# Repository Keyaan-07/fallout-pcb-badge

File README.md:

# Fallout PCB Badges!!

Okay so i made the fallout badge(and everyone else who is a participant made it) andddd i added some unique that that i guess no one might have it. It is decent, it uses an stm32f030.  
So the idea i got for the LED matrix was like when i was talking to zach. He was like what are you doing unique in your PCB Badge, so i just formed the idea instantly in my mind and i stuck with it.  
Also, while writing this, i got the idea to like add an e-ink, so i am probably gonna add it later, i am really tired rn. I will be buying parts myself. yayay. The bom is js the one that the JLC fab toolkit makes sorry if it's not enough :(

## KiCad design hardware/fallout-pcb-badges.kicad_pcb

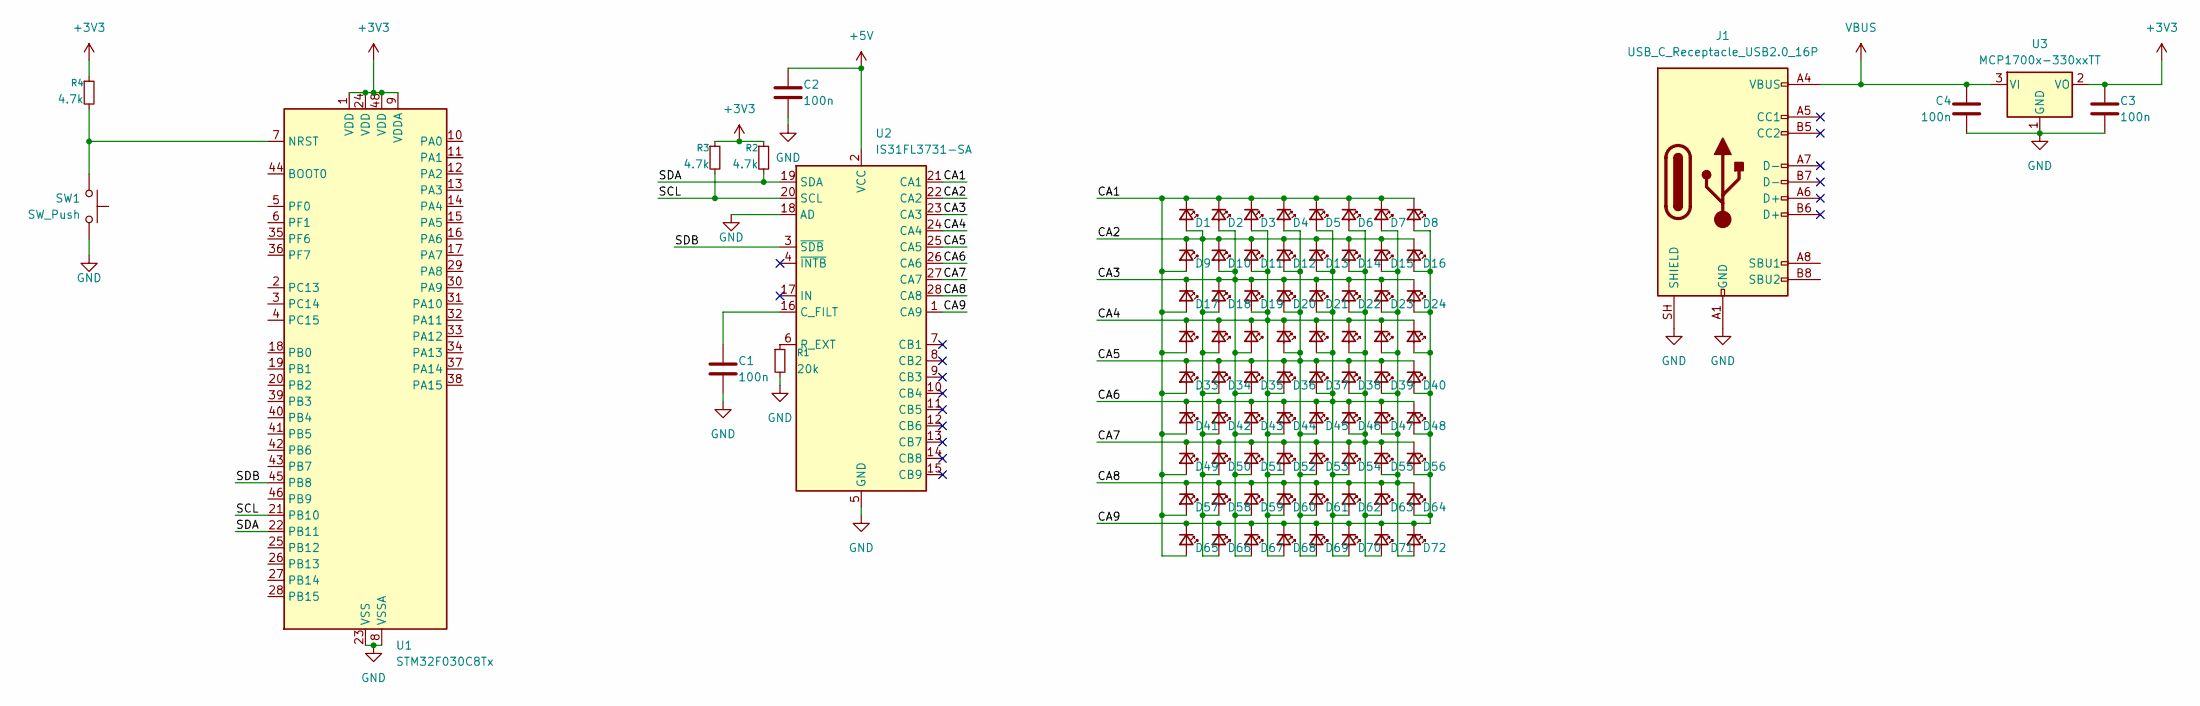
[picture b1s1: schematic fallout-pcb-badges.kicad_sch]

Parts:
C1, C2, C3, C4: 100n; C_0402_1005Metric
D1, D2, D3, D4, D5, D6, D7, D8, D9, D10, D11, D12, D13, D14, D15, D16, D17, D18, D19, D20, D21, D22, D23, D24, D25, D26, D27, D28, D29, D30, D31, D32, D33, D34, D35, D36, D37, D38, D39, D40, D41, D42, D43, D44, D45, D46, D47, D48, D49, D50, D51, D52, D53, D54, D55, D56, D57, D58, D59, D60, D61, D62, D63, D64, D65, D66, D67, D68, D69, D70, D71, D72: LED_Small; LED_0402_1005Metric
J1: USB_C_Receptacle_USB2.0_16P; USB_C_Receptacle_XKB_U262-16XN-4BVC11
R1: 20k; R_0402_1005Metric
R2, R3, R4: 4.7k; R_0402_1005Metric
SW1: SW_Push; SW_SPST_PTS810
U1: STM32F030C8Tx; LQFP-48_7x7mm_P0.5mm
U2: IS31FL3731-SA; SSOP-28_5.3x10.2mm_P0.65mm
U3: MCP1700x-330xxTT; SOT-23

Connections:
+3V3: C3.1, R2.1, R3.1, R4.1, U1.1 (VDD), U1.9 (VDDA), U1.24 (VDD), U1.48 (VDD), U3.2 (VO)
+5V: C2.1, U2.2 (VCC)
/CA1: D1.1 (K), D2.1 (K), D3.1 (K), D4.1 (K), D5.1 (K), D6.1 (K), D7.1 (K), D8.1 (K), D9.2 (A), D17.2 (A), D25.2 (A), D33.2 (A), D41.2 (A), D49.2 (A), D57.2 (A), D65.2 (A), U2.21 (CA1)
/CA2: D1.2 (A), D9.1 (K), D10.1 (K), D11.1 (K), D12.1 (K), D13.1 (K), D14.1 (K), D15.1 (K), D16.1 (K), D18.2 (A), D26.2 (A), D34.2 (A), D42.2 (A), D50.2 (A), D58.2 (A), D66.2 (A), U2.22 (CA2)
/CA3: D2.2 (A), D10.2 (A), D17.1 (K), D18.1 (K), D19.1 (K), D20.1 (K), D21.1 (K), D22.1 (K), D23.1 (K), D24.1 (K), D27.2 (A), D35.2 (A), D43.2 (A), D51.2 (A), D59.2 (A), D67.2 (A), U2.23 (CA3)
/CA4: D3.2 (A), D11.2 (A), D19.2 (A), D25.1 (K), D26.1 (K), D27.1 (K), D28.1 (K), D29.1 (K), D30.1 (K), D31.1 (K), D32.1 (K), D36.2 (A), D44.2 (A), D52.2 (A), D60.2 (A), D68.2 (A), U2.24 (CA4)
/CA5: D4.2 (A), D12.2 (A), D20.2 (A), D28.2 (A), D33.1 (K), D34.1 (K), D35.1 (K), D36.1 (K), D37.1 (K), D38.1 (K), D39.1 (K), D40.1 (K), D45.2 (A), D53.2 (A), D61.2 (A), D69.2 (A), U2.25 (CA5)
/CA6: D5.2 (A), D13.2 (A), D21.2 (A), D29.2 (A), D37.2 (A), D41.1 (K), D42.1 (K), D43.1 (K), D44.1 (K), D45.1 (K), D46.1 (K), D47.1 (K), D48.1 (K), D54.2 (A), D62.2 (A), D70.2 (A), U2.26 (CA6)
/CA7: D6.2 (A), D14.2 (A), D22.2 (A), D30.2 (A), D38.2 (A), D46.2 (A), D49.1 (K), D50.1 (K), D51.1 (K), D52.1 (K), D53.1 (K), D54.1 (K), D55.1 (K), D56.1 (K), D63.2 (A), D71.2 (A), U2.27 (CA7)
/CA8: D7.2 (A), D15.2 (A), D23.2 (A), D31.2 (A), D39.2 (A), D47.2 (A), D55.2 (A), D57.1 (K), D58.1 (K), D59.1 (K), D60.1 (K), D61.1 (K), D62.1 (K), D63.1 (K), D64.1 (K), D72.2 (A), U2.28 (CA8)
/CA9: D8.2 (A), D16.2 (A), D24.2 (A), D32.2 (A), D40.2 (A), D48.2 (A), D56.2 (A), D64.2 (A), D65.1 (K), D66.1 (K), D67.1 (K), D68.1 (K), D69.1 (K), D70.1 (K), D71.1 (K), D72.1 (K), U2.1 (CA9)
/SCL: R3.2, U1.21 (PB10), U2.20 (SCL)
/SDA: R2.2, U1.22 (PB11), U2.19 (SDA)
/SDB: U1.45 (PB8), U2.3 (~SDB)
GND: C1.2, C2.2, C3.2, C4.2, J1.A1 (GND), J1.A12 (GND), J1.B1 (GND), J1.B12 (GND), J1.SH (SHIELD), R1.2, SW1.1, U1.8 (VSSA), U1.23 (VSS), U1.47 (VSS), U2.5 (GND), U2.18 (AD), U3.1 (GND)
unnamed: R4.2, SW1.2, U1.7 (NRST)
unnamed: C1.1, U2.16 (C_FILT)
unnamed: R1.1, U2.6 (R_EXT)
VBUS: C4.1, J1.A4 (VBUS), J1.A9 (VBUS), J1.B4 (VBUS), J1.B9 (VBUS), U3.3 (VI)

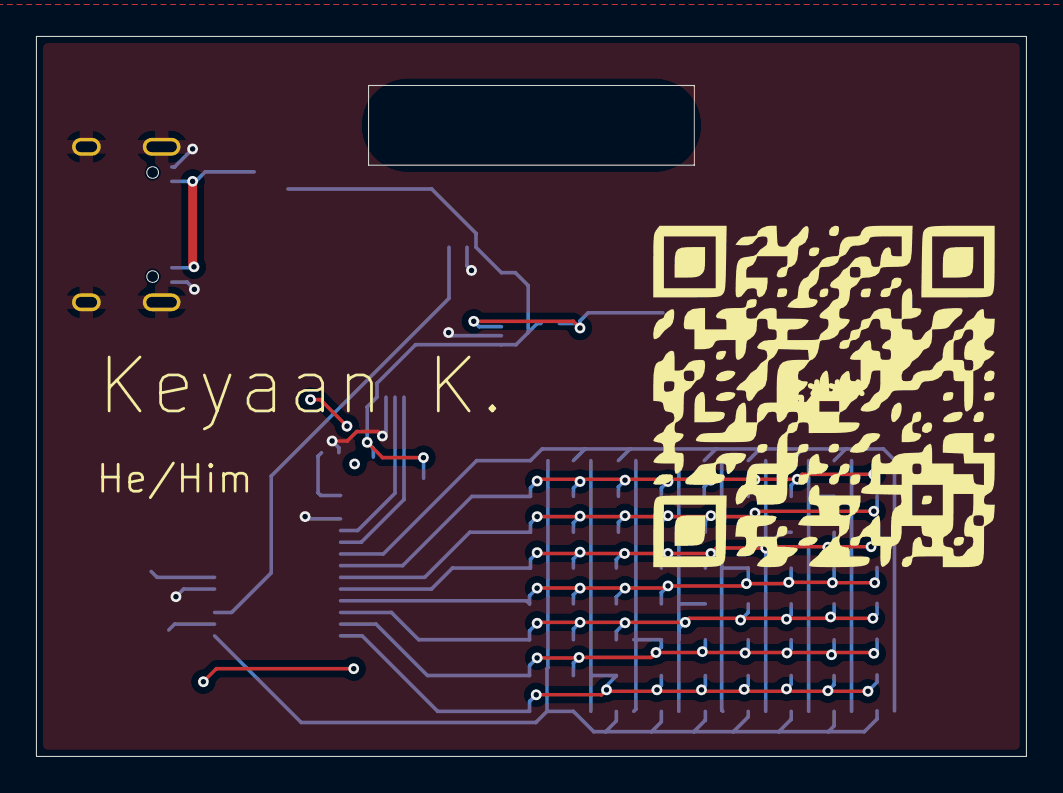
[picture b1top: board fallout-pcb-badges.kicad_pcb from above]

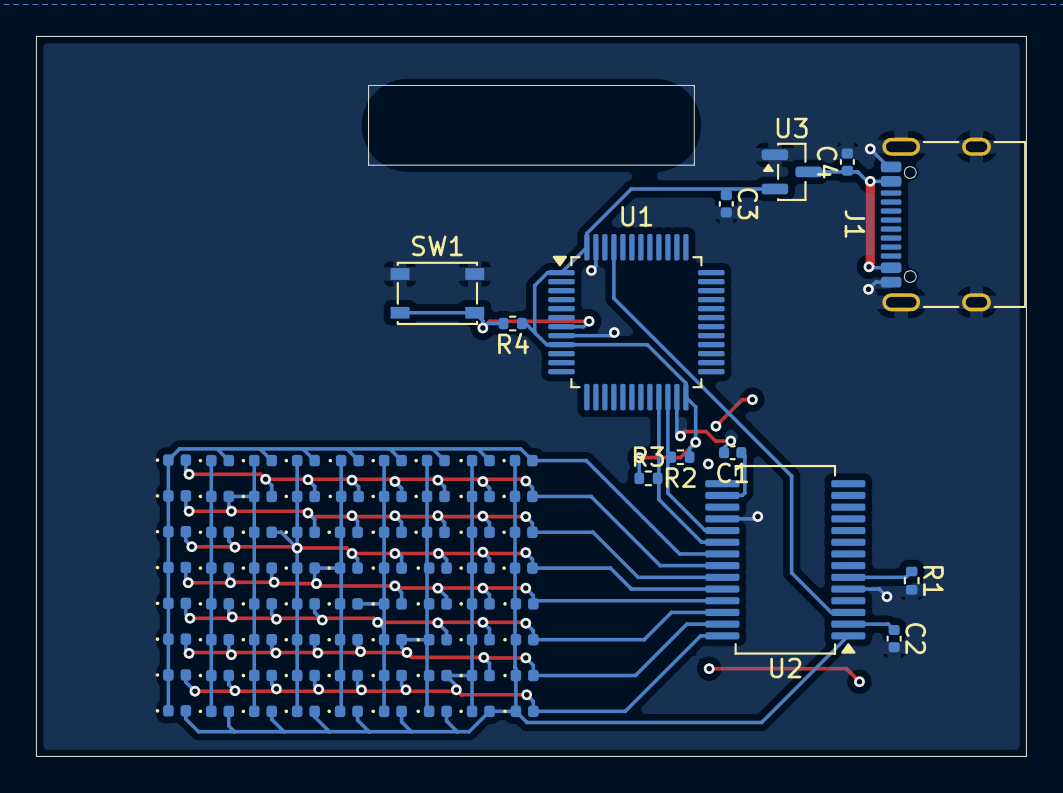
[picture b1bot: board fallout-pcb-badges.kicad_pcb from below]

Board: 2 copper layers, 55.0 x 40.0 mm, 85 parts (85 on the bottom side), 19 nets.

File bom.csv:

Designator,Footprint,Quantity,Value,LCSC Part #
"C1, C2, C3, C4",0402,4,100n,
"D1, D10, D11, D12, D13, D14, D15, D16, D17, D18, D19, D2, D20, D21, D22, D23, D24, D25, D26, D27, D28, D29, D3, D30, D31, D32, D33, D34, D35, D36, D37, D38, D39, D4, D40, D41, D42, D43, D44, D45, D46, D47, D48, D49, D5, D50, D51, D52, D53, D54, D55, D56, D57, D58, D59, D6, D60, D61, D62, D63, D64, D65, D66, D67, D68, D69, D7, D70, D71, D72, D8, D9",0402,72,LED_Small,
J1,USB_C_Receptacle_XKB_U262-16XN-4BVC11,1,USB_C_Receptacle_USB2.0_16P,
R1,0402,1,20k,
"R2, R3, R4",0402,3,4.7k,
SW1,SW_SPST_PTS810,1,SW_Push,
U1,LQFP-48_7x7mm_P0.5mm,1,STM32F030C8Tx,
U2,SSOP-28_5.3x10.2mm_P0.65mm,1,IS31FL3731-SA,
U3,SOT-23,1,MCP1700x-330xxTT,
